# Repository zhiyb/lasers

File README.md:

# lasers
Playing with dangerous show lasers

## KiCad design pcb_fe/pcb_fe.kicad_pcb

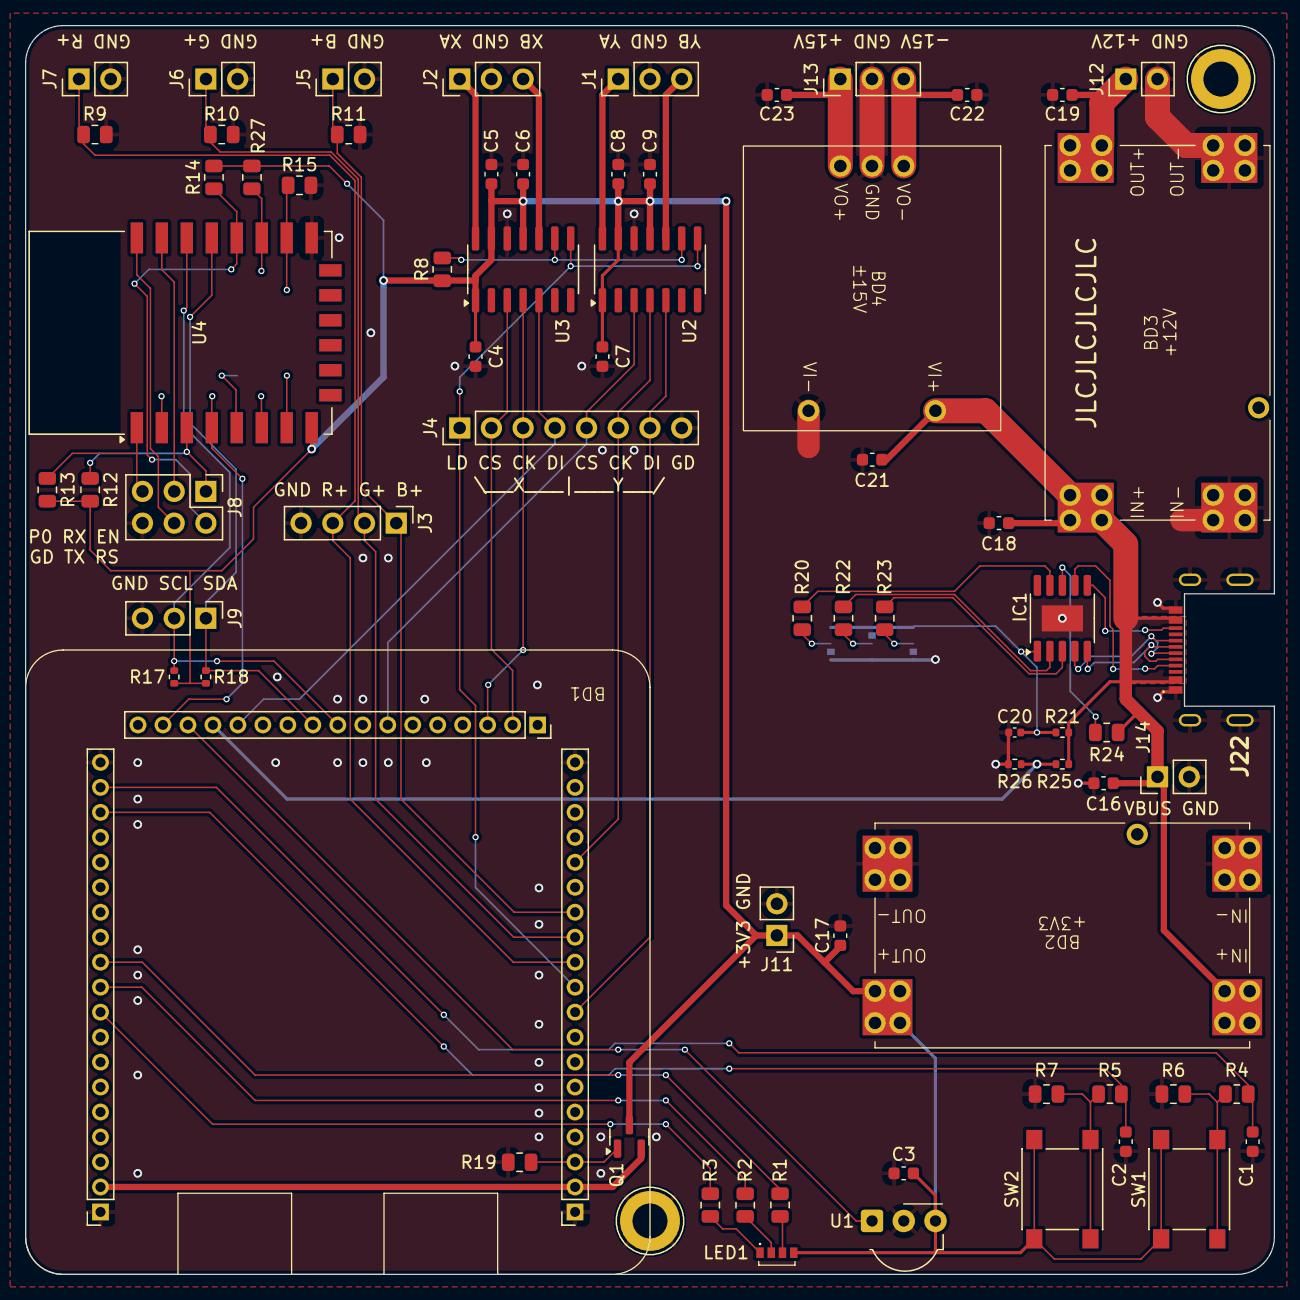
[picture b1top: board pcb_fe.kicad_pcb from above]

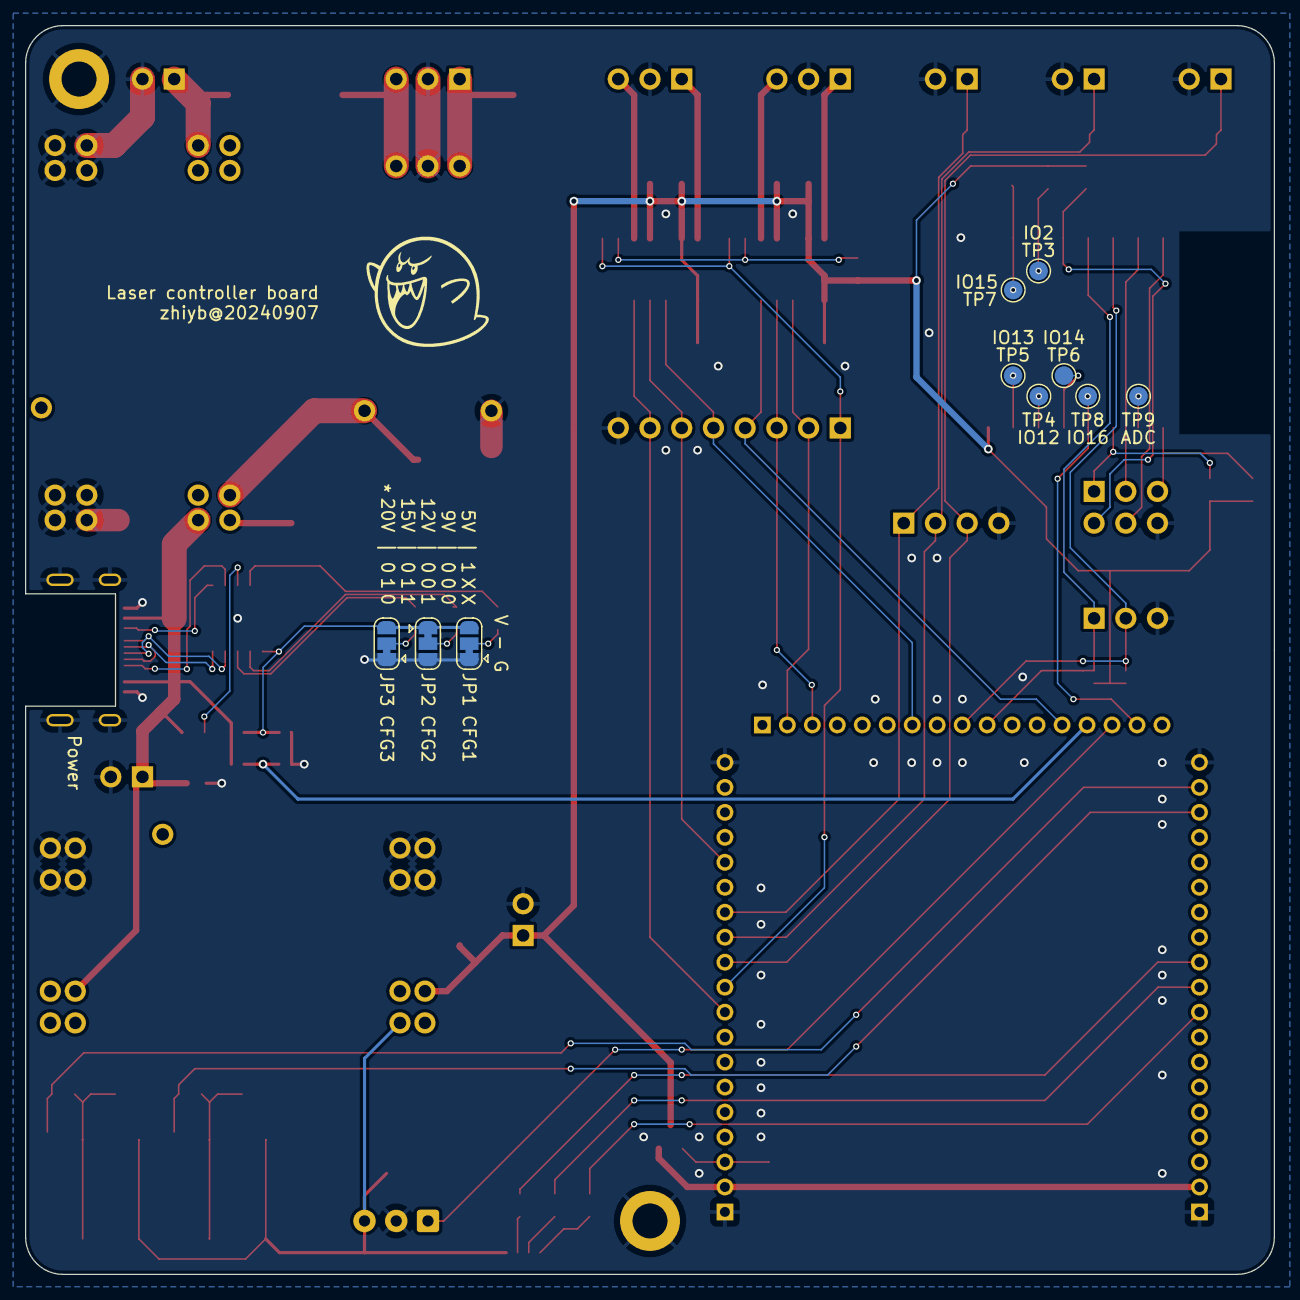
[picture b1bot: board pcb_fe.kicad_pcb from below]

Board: 2 copper layers, 100.0 x 100.0 mm, 82 parts (10 on the bottom side), 61 nets.

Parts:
BD1: STM32F7; BD_STM32F7
BD2: +3V3; Mini560
BD3: +12V; Mini560
BD4: ±15V; DM17
C1, C2, C3, C4, C5, C6, C7, C8, C9, C16, C17, C18, C19, C21, C22, C23: 100n; C_0603_1608Metric
C20: 1u; C_0402_1005Metric
IC1: CH224K; SSOP-10-1EP_3.9x4.9mm_P1mm_EP2.1x3.3mm
J1, J2, J9, J13: Conn_01x03_Pin; PinHeader_1x03_P2.54mm_Vertical
J3: Conn_01x04_Pin; PinHeader_1x04_P2.54mm_Vertical
J4: Conn_01x08_Pin; PinHeader_1x08_P2.54mm_Vertical
J5, J6, J7, J11, J12, J14: Conn_01x02_Pin; PinHeader_1x02_P2.54mm_Vertical
J8: Conn_02x03_Odd_Even; PinHeader_2x03_P2.54mm_Vertical
J10: 216990-0001; 2169900001
JP1, JP2, JP3: SolderJumper_3_Bridged12; SolderJumper-3_P1.3mm_Bridged12_RoundedPad1.0x1.5mm
LED1: MSL0601RGBU1
Q1: DMG2301L; SOT-23
R1, R2, R3: 330; R_0805_2012Metric
R4, R5, R6, R7, R8, R9, R10, R11, R12, R13, R14, R15, R19, R20, R22, R23, R24, R27: 10k; R_0805_2012Metric
R17, R18, R26: 2k2; R_0402_1005Metric
R21: 1k; R_0402_1005Metric
R25: 20k; R_0402_1005Metric
SW1, SW2: SW_Push; SW_Push_1P1T_NO_6x6mm_H9.5mm
TP1, TP2: TestPoint_Probe; TestPoint_Loop_D3.80mm_Drill2.8mm
TP3, TP4, TP5, TP6, TP7, TP8, TP9: TestPoint; TestPoint_Pad_D1.5mm
U1: TSDP341xx; Vishay_MOLD-3Pin
U2, U3: MCP4922; SOIC-14_3.9x8.7mm_P1.27mm
U4: ESP-12F; ESP-12E

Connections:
+3V3: BD2.3 (VOUT), C3.1, C4.1, C5.1, C6.1, C7.1, C8.1, C9.1, C17.1, J11.1, LED1.1 (COMMON_A), Q1.3 (D), R8.1, R12.2, R13.2, R14.2, R17.1, R18.1, R27.2, SW1.1, SW2.1, U1.3 (Vs), U2.1 (Vdd), U2.11 (VrefB), U2.13 (VrefA), U3.1 (Vdd), U3.11 (VrefB), U3.13 (VrefA), U4.8 (VCC)
+12V: BD3.3 (VOUT), C19.1, J12.1
+15V: BD4.3 (VO+), C23.1, J13.1
-15V: BD4.4 (VO-), C22.1, J13.3
/BTN_1: BD1.54 (PC13), C1.1, R4.2
/BTN_2: BD1.53 (PC14), C2.1, R5.2
/IR: BD1.34 (PA7), U1.1 (OUT)
/Power/CFG1: IC1.9 (CFG1), R20.2
/Power/CFG2: IC1.2 (CFG2), R22.2
/Power/CFG3: IC1.3 (CFG3), R23.2
/Power/CH_VDD: C20.1, IC1.1 (VDD), JP1.3 (B), JP2.1 (A), JP3.3 (B), R21.2
/Power/P_CC1: IC1.7 (CC1), J10.A5 (CC1)
/Power/P_CC2: IC1.6 (CC2), J10.B5 (CC2)
/Power/P_DM: IC1.5 (DM), J10.A7 (DN1), J10.B7 (DN2)
/Power/P_DP: IC1.4 (DP), J10.A6 (DP1), J10.B6 (DP2)
/STM32F7/ESP8266/ADC: TP9.1, U4.2 (ADC)
/STM32F7/ESP8266/EN: J8.1, R12.1, U4.3 (EN)
/STM32F7/ESP8266/GPIO0: J8.2, R14.1, U4.18 (GPIO0)
/STM32F7/ESP8266/GPIO1: J8.4, U4.22 (GPIO1/TXD)
/STM32F7/ESP8266/GPIO2: R27.1, TP3.1, U4.17 (GPIO2)
/STM32F7/ESP8266/GPIO3: J8.3, U4.21 (GPIO3/RXD)
/STM32F7/ESP8266/GPIO12: TP4.1, U4.6 (GPIO12)
/STM32F7/ESP8266/GPIO13: TP5.1, U4.7 (GPIO13)
/STM32F7/ESP8266/GPIO14: TP6.1, U4.5 (GPIO14)
/STM32F7/ESP8266/GPIO15: R15.2, TP7.1, U4.16 (GPIO15)
/STM32F7/ESP8266/RST: J8.5, R13.1, U4.1 (~RST)
/STM32F7/F7PA0: BD1.47 (PA0), R1.1
/STM32F7/F7PA1: BD1.46 (PA1), R2.1
/STM32F7/F7PA2: BD1.45 (PA2), R3.1
/STM32F7/F7PA6: BD1.35 (PA6), TP8.1, U4.4 (GPIO16)
/STM32F7/F7PA9: BD1.15 (PA9), J4.6, U2.4 (SCK)
/STM32F7/F7PA15: BD1.21 (PA15), J4.2, U3.3 (~CS)
/STM32F7/F7PB2: BD1.32 (PB2), J4.4, U3.5 (SDI)
/STM32F7/F7PB4: BD1.26 (PB4), J4.5, U2.3 (~CS)
/STM32F7/F7PB6: BD1.28 (PB6), J9.2, R17.2, U4.20 (GPIO5)
/STM32F7/F7PB7: BD1.29 (PB7), J9.1, R18.2, U4.19 (GPIO4)
/STM32F7/F7PB15: BD1.9 (PB15), J4.7, U2.5 (SDI)
/STM32F7/F7PC6: BD1.10 (PC6), J4.1, U2.8 (~LDAC), U3.8 (~LDAC)
/STM32F7/F7PC7: BD1.11 (PC7), J3.3, J7.1, R9.1
/STM32F7/F7PC8: BD1.12 (PC8), J3.2, J6.1, R10.1
/STM32F7/F7PC9: BD1.13 (PC9), J3.1, J5.1, R11.1
/STM32F7/F7PC10: BD1.22 (PC10), J4.3, U3.4 (SCK)
/STM32F7/Laser DAC/SHDN: R8.2, U2.9 (~SHDN), U3.9 (~SHDN)
/STM32F7/VF7: BD1.2 (VF7), BD1.38 (VF7), Q1.2 (S)
/STM32F7/VF7_VBUS: BD1.3 (VF7_VBUS), Q1.1 (G), R19.2
/VSENSE: BD1.33 (PC4), R25.2, R26.1
GND: BD1.1 (GND), BD1.19 (GND), BD1.37 (GND), BD1.55 (GND), BD2.2 (GND), BD3.2 (GND), BD4.2 (GND), C1.2, C2.2, C3.2, C4.2, C5.2, C6.2, C7.2, C8.2, C9.2, C16.2, C17.2, C18.2, C19.2, C20.2, C21.2, C22.2, C23.2, IC1.11 (GND), J1.2, J2.2, J3.4, J4.8, J5.2, J6.2, J7.2, J8.6, J9.3, J10.A1 (GND_1), J10.A12 (GND_2), J10.B1 (GND_3), J10.B12 (GND_4), J10.MH1, J10.MH2, J10.MH3, J10.MH4, J11.2, J12.2, J13.2, J14.2, JP1.1 (A), JP2.3 (B), JP3.1 (A), R6.2, R7.2, R9.2, R10.2, R11.2, R15.1, R19.1, R26.2, TP1.1, TP2.1, U1.2 (GND), U2.12 (Vss), U3.12 (Vss), U4.15 (GND)
unnamed: IC1.8 (VBUS), R24.2
unnamed: J1.1, U2.14 (VA)
unnamed: J1.3, U2.10 (VB)
unnamed: J2.1, U3.14 (VA)
unnamed: J2.3, U3.10 (VB)
unnamed: JP1.2 (C), R20.1
unnamed: JP2.2 (C), R22.1
unnamed: JP3.2 (C), R23.1
unnamed: LED1.3 (K_BLUE), R2.2
unnamed: LED1.2 (K_GREEN), R1.2
unnamed: LED1.4 (K_RED), R3.2
unnamed: R4.1, R6.1, SW1.2
unnamed: R5.1, R7.1, SW2.2
VBUS: BD2.1 (VIN), BD3.1 (VIN), BD4.1 (VI+), C16.1, C18.1, C21.1, J10.A4 (VBUS_1), J10.A9 (VBUS_2), J10.B4 (VBUS_3), J10.B9 (VBUS_4), J14.1, R21.1, R24.1, R25.1

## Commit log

2024-09-13 pcb_fe: Version 20240907
